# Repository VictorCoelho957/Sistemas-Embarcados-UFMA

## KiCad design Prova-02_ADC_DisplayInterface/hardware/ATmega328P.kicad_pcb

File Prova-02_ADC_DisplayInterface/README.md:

# Prova 02: Calculadora Binária com Máquina de Estados 🧮

Desenvolvimento de uma calculadora funcional para soma de dois números (0 a 3) utilizando o microcontrolador *ATmega328P*.

## 🛠️ Requisitos de Hardware (KiCad)

Arquitetura Mínima: Uso do ATmega328P com cristal externo e capacitores de carga.

Gestão de Energia Regulador de tensão para 5V e capacitores de desacoplamento, com bornes para alimentação externa (7-12V).

Interface Display de 7 segmentos (catodo comum) para entrada e 3 LEDs para o resultado da soma em binário .

## ⚙️ Firmware e Lógica

Máquina de Estados O sistema alterna entre entrada do Valor 1, Valor 2 e exibição do Resultado.

Debounce Implementação de filtro via temporização (delay) para garantir a leitura correta dos botões.

Lógica Binária O resultado da soma é processado e decomposto em bits para acionamento individual dos LEDs.

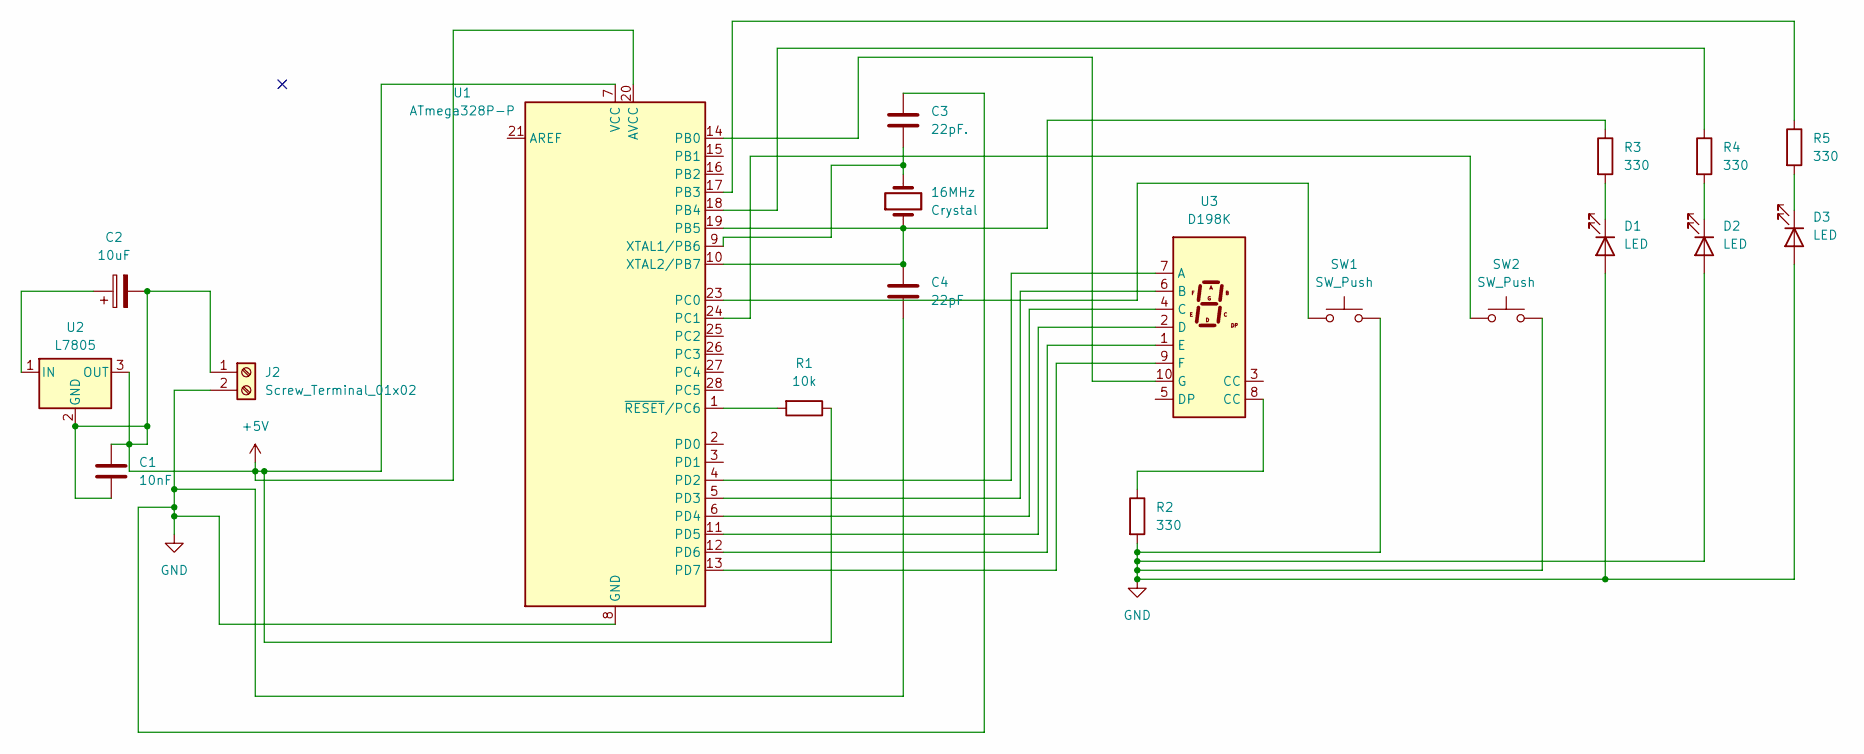
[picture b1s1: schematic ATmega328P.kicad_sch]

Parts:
16MHz: Crystal; Crystal_HC49-4H_Vertical
C1: 10nF; C_Disc_D3.0mm_W1.6mm_P2.50mm
C2: 10uF; C_Radial_D5.0mm_H5.0mm_P2.00mm
C3: 22pF.; C_Disc_D3.0mm_W1.6mm_P2.50mm
C4: 22pF; C_Disc_D3.0mm_W1.6mm_P2.50mm
D1, D2, D3: LED; LED_D5.0mm
J2: Screw_Terminal_01x02; TerminalBlock_Phoenix_PT-1,5-2-5.0-H_1x02_P5.00mm_Horizontal
R1: 10k; R_Axial_DIN0207_L6.3mm_D2.5mm_P7.62mm_Horizontal
R2, R3, R4, R5: 330; R_Axial_DIN0207_L6.3mm_D2.5mm_P7.62mm_Horizontal
SW1, SW2: SW_Push; SW_PUSH_6mm
U1: ATmega328P-P; DIP-28_W7.62mm
U2: L7805; TO-220-3_Vertical
U3: D198K; D1X8K

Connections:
+5V: C1.1, C1.2, C2.2, J2.1, R1.1, U1.7 (VCC), U1.20 (AVCC), U2.2 (GND), U2.3 (OUT)
GND: C3.1, C4.2, D1.2 (A), D2.2 (A), D3.2 (A), J2.2, R2.2, SW1.2, SW2.2, U1.8 (GND), U1.22 (GND)
unnamed: D1.1 (K), R3.2
unnamed: D2.1 (K), R4.2
unnamed: D3.1 (K), R5.2
unnamed: R2.1, U3.8 (CC)
unnamed: U1.14 (PB0), U3.10 (G)
unnamed: R5.1, U1.17 (PB3)
unnamed: R4.1, U1.18 (PB4)
unnamed 9: 16MHz.1, C4.1, R3.1, U1.10 (XTAL2/PB7), U1.19 (PB5); also elsewhere on the board
unnamed: SW1.1, U1.23 (PC0)
unnamed: SW2.1, U1.24 (PC1)
unnamed: U1.4 (PD2), U3.7 (A)
unnamed: U1.5 (PD3), U3.6 (B)
unnamed: U1.6 (PD4), U3.4 (C)
unnamed: U1.11 (PD5), U3.2 (D)
unnamed: U1.12 (PD6), U3.1 (E)
unnamed: U1.13 (PD7), U3.9 (F)
unnamed 18: 16MHz.2, C3.2, U1.9 (XTAL1/PB6); also elsewhere on the board
unnamed: R1.2, U1.1 (~RESET/PC6)
unnamed: C2.1, U2.1 (IN)

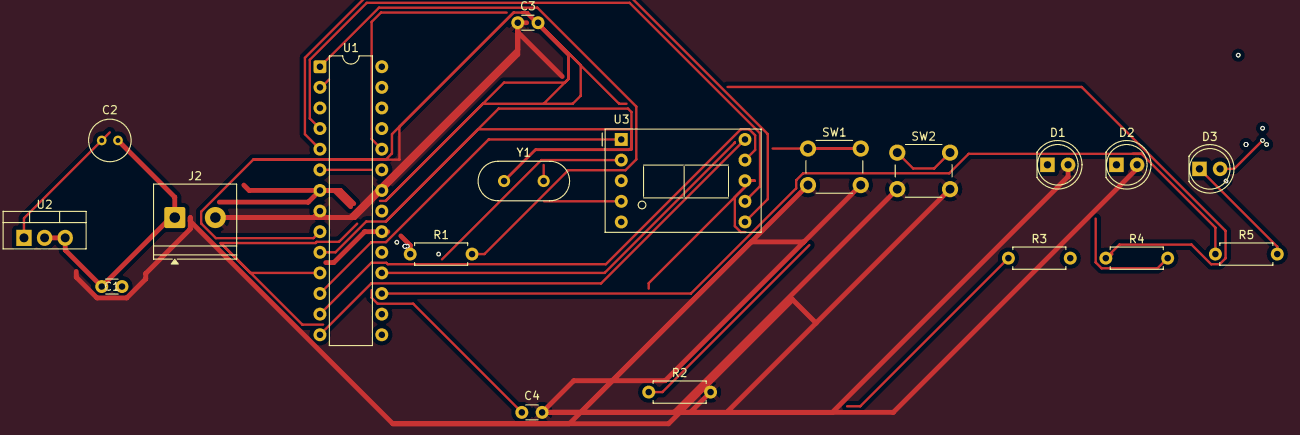
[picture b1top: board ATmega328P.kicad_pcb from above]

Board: 2 copper layers, 19 parts (0 on the bottom side), 21 nets.

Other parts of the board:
Y1: Crystal; Crystal_HC49-4H_Vertical

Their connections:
unnamed 9: Y1.1; also elsewhere on the board
unnamed 18: Y1.2; also elsewhere on the board

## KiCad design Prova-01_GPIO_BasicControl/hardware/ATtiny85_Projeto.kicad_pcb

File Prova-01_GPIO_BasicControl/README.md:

# Prova 01: Controle de GPIO com ATtiny85 e Regulagem de Tensão 💡

Este projeto demonstra o controle de baixo nível (Bare Metal) do microcontrolador **ATtiny85**, focando na manipulação direta de registradores e no projeto de hardware para alimentação estável.

## 🛠️ Especificações Técnicas
* **Microcontrolador:** ATtiny85 (Arquitetura AVR RISC).
* **Linguagem:** C com manipulação direta de registradores (DDR/PORT).
* **Gestão de Energia:** Implementação de regulador de tensão **L7805** para converter entrada DC em 5V estáveis, protegida por capacitores de desacoplamento.

## ⚙️ Implementação de Firmware
Diferente do uso de funções de abstração (como `pinMode`), o código utiliza escrita direta nos registradores de I/O para maior eficiência:
* **DDRB (Data Direction Register B):** Configurado como `0xFF` para definir todos os pinos como saída.
* **PORTB:** Utilizado para alternar os estados lógicos (High/Low) dos pinos com temporização via `_delay_ms`.

## 📐 Design de Hardware (KiCad)
O projeto inclui o ciclo completo de desenvolvimento de hardware:
1.  **Esquema Elétrico:** Proteção de entrada com diodo e filtragem com capacitores eletrolíticos.
2.  **Layout de PCB:** Roteamento otimizado para dimensões reduzidas, ideal para sistemas embarcados compactos.
3.  **Visualização 3D:** Validação mecânica dos componentes instalados.

## 📺 Simulação
A lógica foi validada via **Tinkercad** antes da prototipagem física, garantindo a correta polarização do LED através de resistor limitador calculado por:
$$R = \frac{V_{cc} - V_{led}}{I_{led}}$$

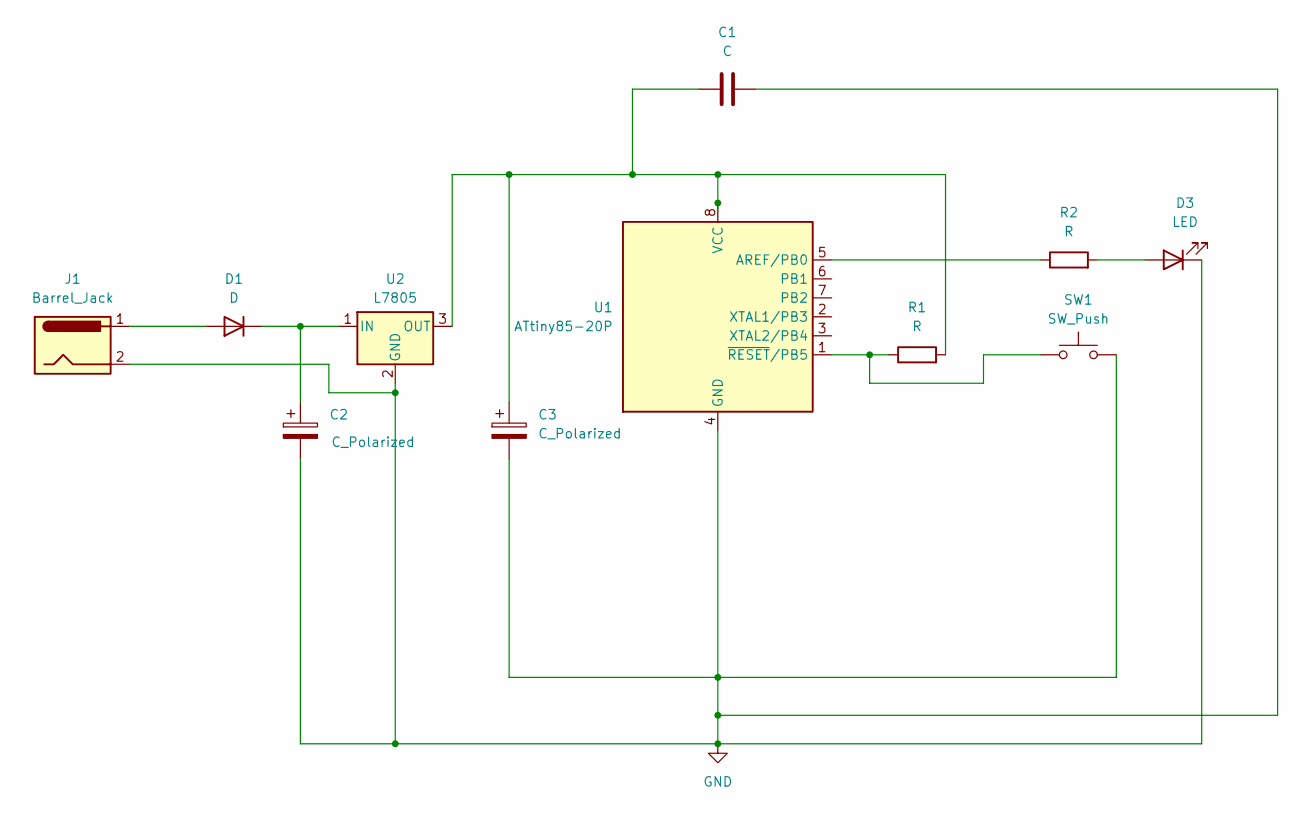
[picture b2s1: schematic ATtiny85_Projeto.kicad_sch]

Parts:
C1: C; C_Disc_D5.0mm_W2.5mm_P5.00mm
C2, C3: C_Polarized; CP_Radial_D5.0mm_P2.50mm
D1: D; D_DO-41_SOD81_P10.16mm_Horizontal
D3: LED; LED_D5.0mm
J1: Barrel_Jack; BarrelJack_Horizontal
R1, R2: R; R_Axial_DIN0207_L6.3mm_D2.5mm_P7.62mm_Horizontal
SW1: SW_Push; SW_PUSH_6mm
U1: ATtiny85-20P; DIP-8_W7.62mm
U2: L7805; TO-220-3_Vertical

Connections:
GND: C1.2, C2.2, C3.2, D3.1 (K), J1.2, SW1.2, U1.4 (GND), U2.2 (GND)
unnamed: D1.2 (A), J1.1
unnamed: C2.1, D1.1 (K), U2.1 (IN)
unnamed: D3.2 (A), R2.2
unnamed: R2.1, U1.5 (AREF/PB0)
unnamed: C1.1, C3.1, R1.2, U1.8 (VCC), U2.3 (OUT)
unnamed: R1.1, SW1.1, U1.1 (~RESET/PB5)

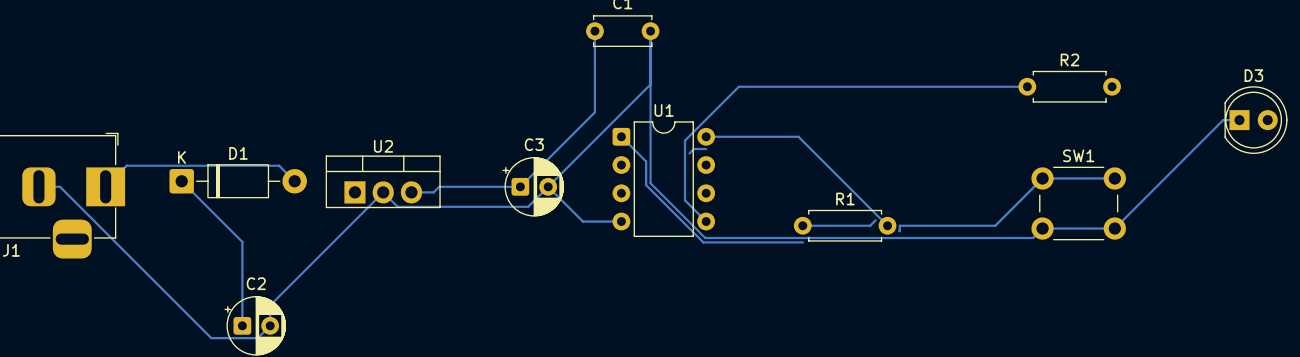
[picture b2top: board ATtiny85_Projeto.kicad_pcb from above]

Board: 2 copper layers, 11 parts (0 on the bottom side), 7 nets.

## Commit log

2026-01-19 Versão Final: Portfólio de Avaliações LabSECI - UFMA
2026-01-19 Provas 01 e 02
2026-01-24 Organizando Prova 01 com KiCad e ATtiny85
2026-01-24 Adicionando Prova 02
2026-01-24 Finalizando README Geral e Portfólio
2026-04-26 Fix formatting and citations in README.md
